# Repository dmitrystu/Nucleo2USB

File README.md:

## NUCLEO2USB SHIELD

+ Compatible with NUCLEO-64 boards
+ Can be configured as 2xOTGFS, 1xOTGFS, 2xDEVFS, 1xDEVFS, 1xDEVFS+1xOTGFS
+ Can provide power to the baseboard from USB1 USB2 and STLINK(U5V) via E5V pin
+ USB FS/LS override jumper (for the NUCLEO-F303RE / NUCLEO-F103RB)
+ 2x micro USB TYPE B connectors
+ ESCDA5V3SC6 USB ESD protection
+ LM3526L USB-OTG power switch with over-current protection

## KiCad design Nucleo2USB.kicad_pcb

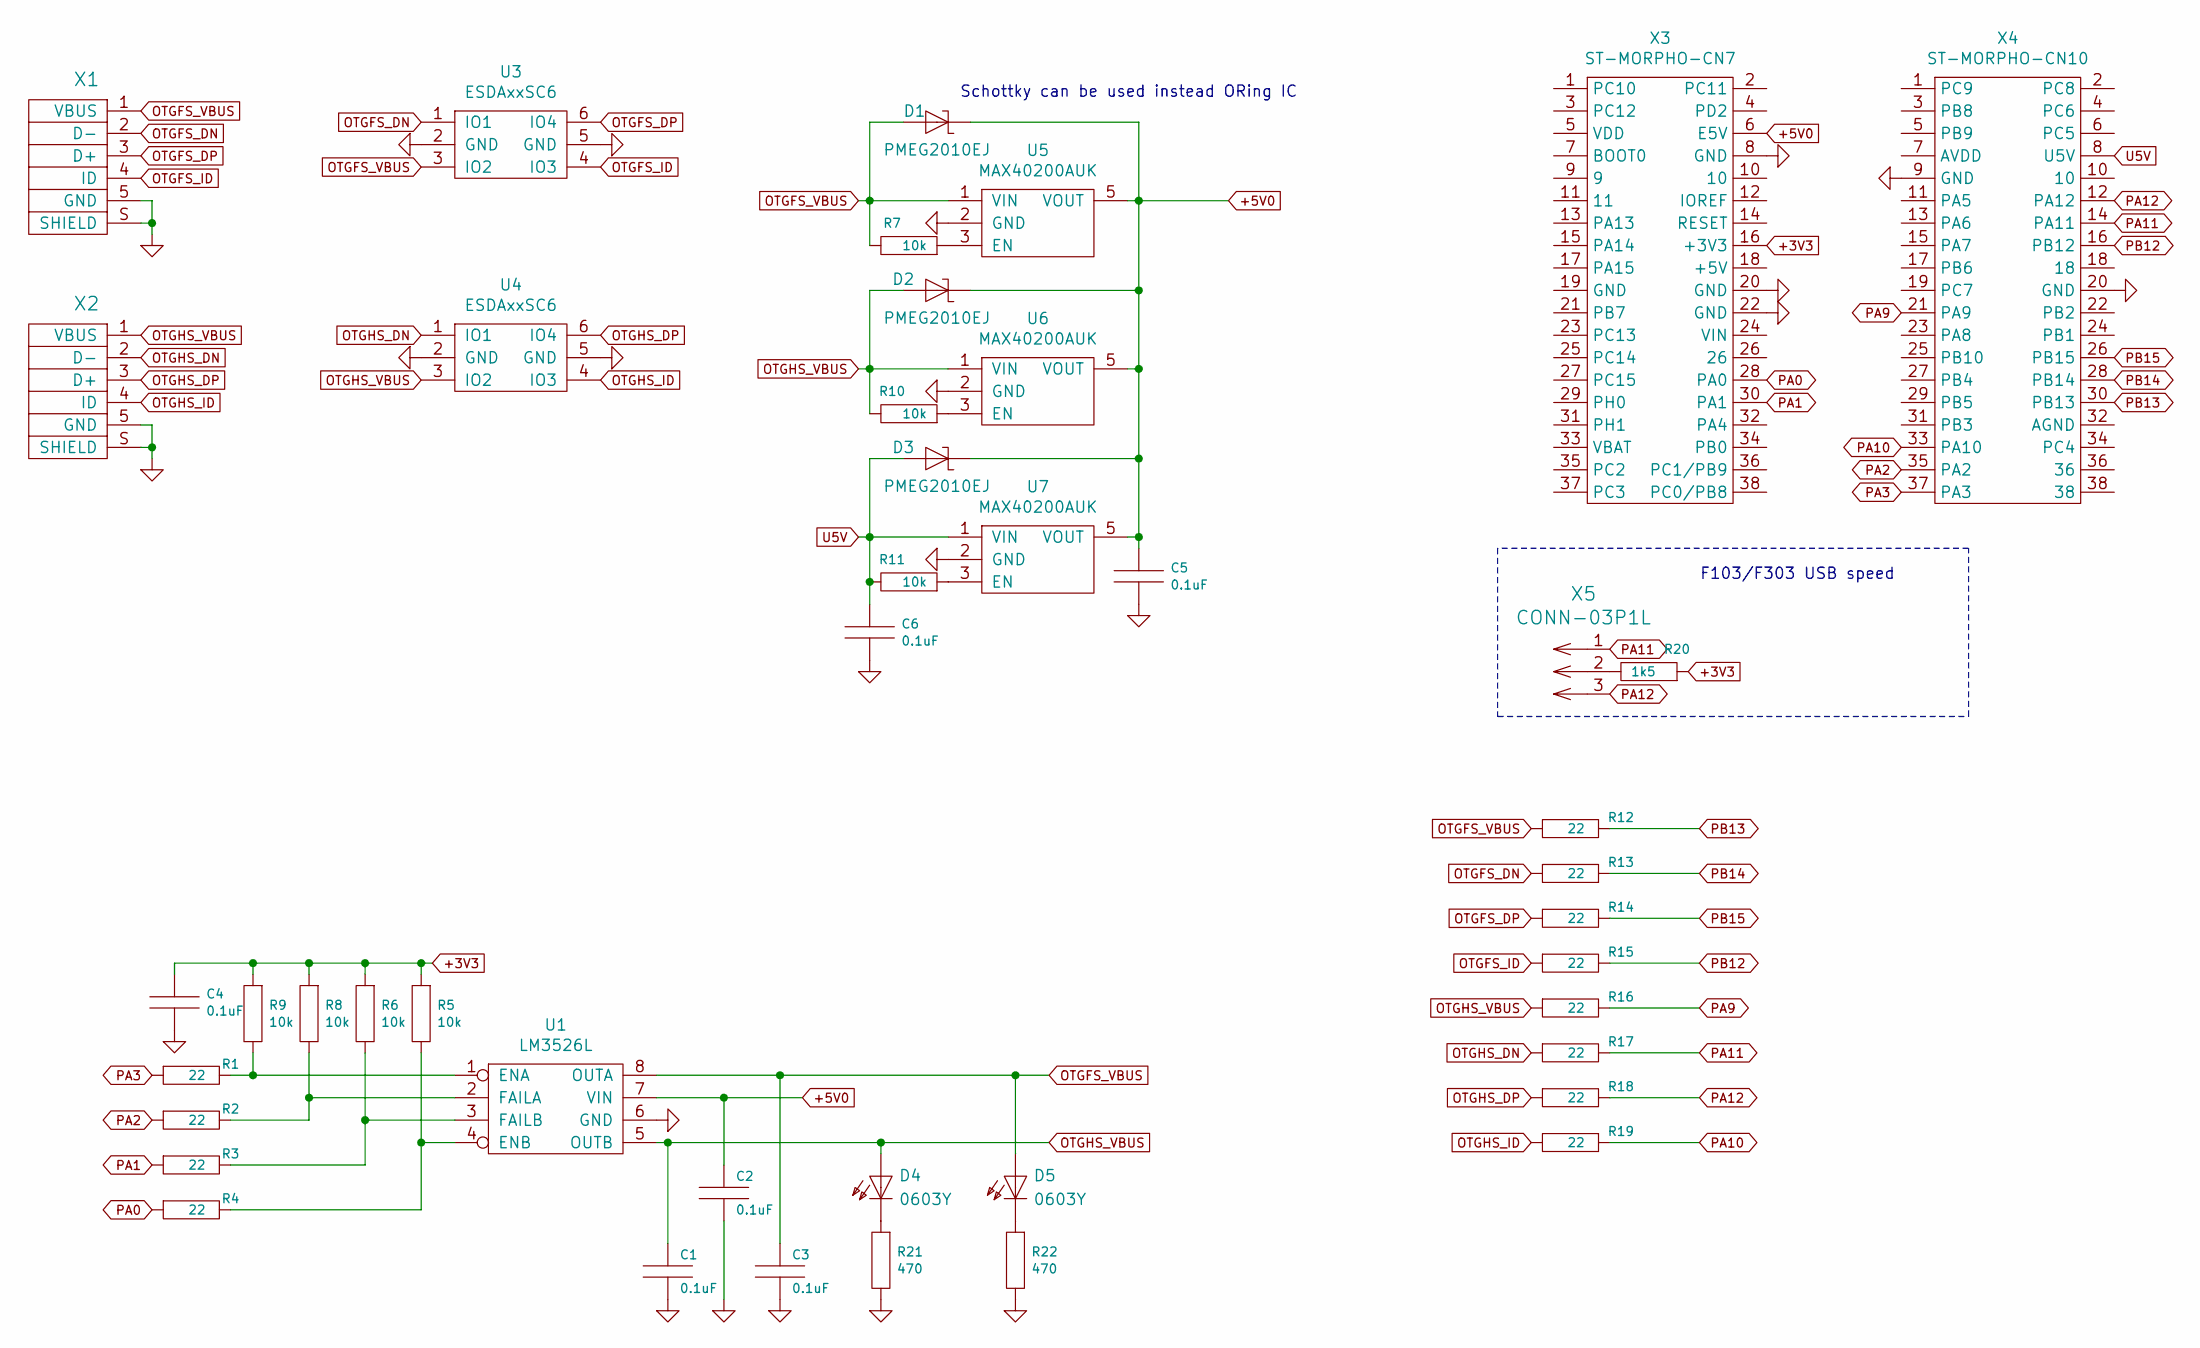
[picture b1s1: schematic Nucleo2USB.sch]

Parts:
C1, C2, C3, C4, C5, C6: 0.1uF; SMD-0603C
D1, D2, D3: PMEG2010EJ; SOD-123F
D4, D5: 0603Y; LED-0603
R1, R2, R3, R4, R12, R13, R14, R15, R16, R17, R18, R19: 22; SMD-0603R
R5, R6, R7, R8, R9, R10, R11: 10k; SMD-0603R
R20: 1k5; SMD-0603R
R21, R22: 470; SMD-0603R
U1: LM3526L; SO65P030X044-8
U3, U4: ESDAxxSC6; SOT-23-6
U5, U6, U7: MAX40200AUK; SOT-23-5
X1, X2: USB-OTG; AMP10118194-0001LF
X3: ST-MORPHO-CN7; DS1023-04-2X19A11
X4: ST-MORPHO-CN10; DS1023-04-2X19A11
X5: CONN-03P1L; DS1021-1X03S61

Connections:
+3V3: C4.1 (C1), R5.1 (R1), R6.1 (R1), R8.1 (R1), R9.1 (R1), R20.1 (R1), X3.16 (+3V3)
+5V0: C2.1 (C1), C5.1 (C1), D1.1 (K), D2.1 (K), D3.1 (K), U1.7 (VIN), U5.5 (VOUT), U6.5 (VOUT), U7.5 (VOUT), X3.6 (E5V)
AGND: C1.2 (C2), C2.2 (C2), C3.2 (C2), C4.2 (C2), C5.2 (C2), C6.2 (C2), R21.2 (R2), R22.2 (R2), U1.6 (GND), U3.2 (GND), U3.5 (GND), U4.2 (GND), U4.5 (GND), U5.2 (GND), U6.2 (GND), U7.2 (GND), X1.5 (GND), X1.S (SHIELD), X2.5 (GND), X2.S (SHIELD), X3.8 (GND), X3.20 (GND), X3.22 (GND), X4.9 (GND), X4.20 (GND)
unnamed: D4.K, R21.1 (R1)
unnamed: D5.K, R22.1 (R1)
unnamed: R1.2 (R2), R9.2 (R2), U1.1 (ENA)
unnamed: R2.2 (R2), R8.2 (R2), U1.2 (FAILA)
unnamed: R3.2 (R2), R6.2 (R2), U1.3 (FAILB)
unnamed: R4.2 (R2), R5.2 (R2), U1.4 (ENB)
unnamed: R7.1 (R1), U5.3 (EN)
unnamed: R10.1 (R1), U6.3 (EN)
unnamed: R11.1 (R1), U7.3 (EN)
unnamed: R20.2 (R2), X5.2
OTGFS_DN: R13.1 (R1), U3.1 (IO1), X1.2 (D-)
OTGFS_DP: R14.1 (R1), U3.6 (IO4), X1.3 (D+)
OTGFS_ID: R15.1 (R1), U3.4 (IO3), X1.4 (ID)
OTGFS_VBUS: C3.1 (C1), D1.2 (A), D5.A, R7.2 (R2), R12.1 (R1), U1.8 (OUTA), U3.3 (IO2), U5.1 (VIN), X1.1 (VBUS)
OTGHS_DN: R17.1 (R1), U4.1 (IO1), X2.2 (D-)
OTGHS_DP: R18.1 (R1), U4.6 (IO4), X2.3 (D+)
OTGHS_ID: R19.1 (R1), U4.4 (IO3), X2.4 (ID)
OTGHS_VBUS: C1.1 (C1), D2.2 (A), D4.A, R10.2 (R2), R16.1 (R1), U1.5 (OUTB), U4.3 (IO2), U6.1 (VIN), X2.1 (VBUS)
PA0: R4.1 (R1), X3.28 (PA0)
PA1: R3.1 (R1), X3.30 (PA1)
PA2: R2.1 (R1), X4.35 (PA2)
PA3: R1.1 (R1), X4.37 (PA3)
PA9: R16.2 (R2), X4.21 (PA9)
PA10: R19.2 (R2), X4.33 (PA10)
PA11: R17.2 (R2), X4.14 (PA11), X5.1
PA12: R18.2 (R2), X4.12 (PA12), X5.3
PB12: R15.2 (R2), X4.16 (PB12)
PB13: R12.2 (R2), X4.30 (PB13)
PB14: R13.2 (R2), X4.28 (PB14)
PB15: R14.2 (R2), X4.26 (PB15)
U5V: C6.1 (C1), D3.2 (A), R11.2 (R2), U7.1 (VIN), X4.8 (U5V)

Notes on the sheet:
F103/F303 USB speed
Schottky can be used instead ORing IC

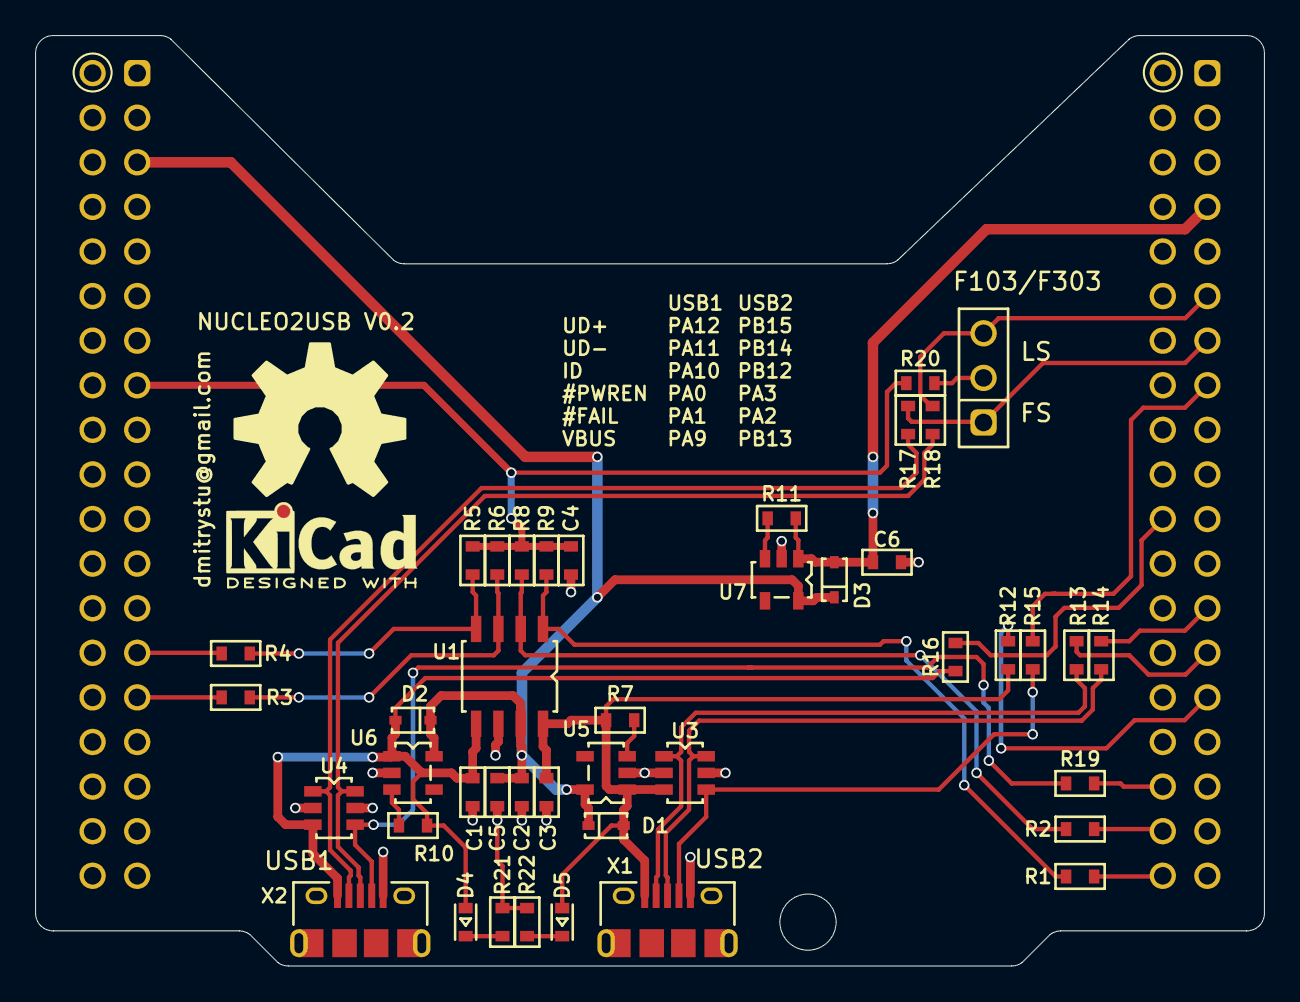
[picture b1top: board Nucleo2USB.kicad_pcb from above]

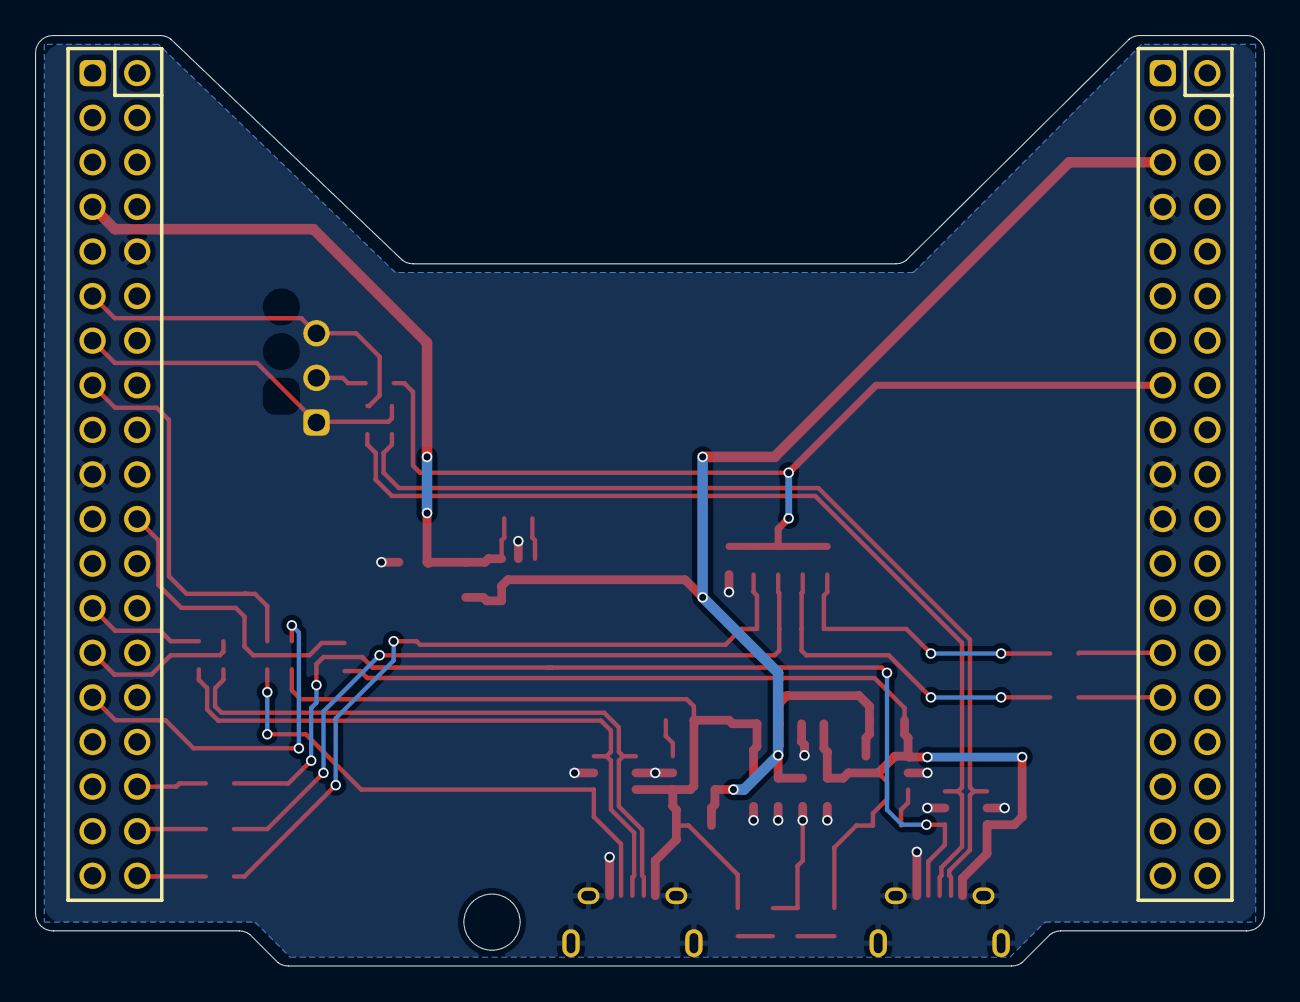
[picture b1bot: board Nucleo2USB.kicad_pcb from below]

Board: 2 copper layers, 70.0 x 53.0 mm, 45 parts (2 on the bottom side), 34 nets.

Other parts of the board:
OSHW_FS_10MM: VAL**; OSHW_FS_10MM

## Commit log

2020-10-12 Initial
2020-10-12 add .gitignore, .gitattributes
2020-10-12 add PDF schematic
2021-02-03 update pcb, add cache library
